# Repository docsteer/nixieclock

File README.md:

# Toms Nixie Clock
This project includes software and hardware designs for a nixie clock based on Raspberry Pi Zero W and IN14 tubes.

The design has hour, minute and second displays, separator digits (IN-1 indicators), and RGB LED underlighting of the tubes.

# Hardware
The hardware folder includes the PCB design files (KiCad format), and a bill of materials with component links to Mouser electronics.

# Software
The software is a Python script that runs on a standard installation of Raspian on a raspberry pi zero W.

It drives the tubes, and controls the LED underlighting based on astrononical time, pre-dawn, after dawn, after noon, after sunset)

It requires the following libraries (which you can install with ```pip install xxx```):

- spidev
- astral
- pytz
- neopixel

# Enclosure
The enclosure design is for laser-cut plywood with suitable openings for the tubes, indicators and support hardware

# License
This project is licensed under a Creative Commons Zero license. Feel free to remix and use as you please.

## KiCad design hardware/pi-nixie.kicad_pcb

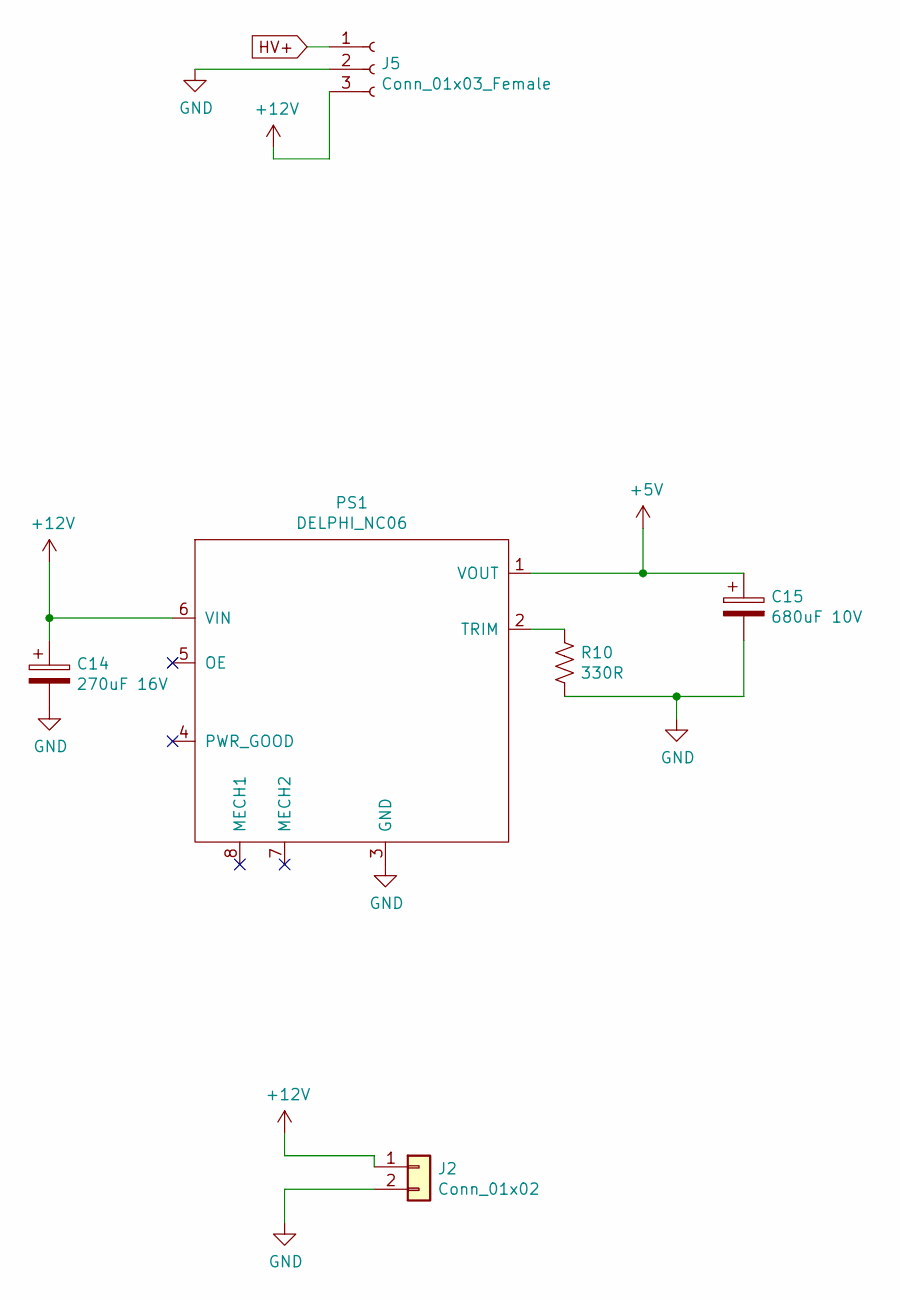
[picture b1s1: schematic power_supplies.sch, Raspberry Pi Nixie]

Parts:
C14: 270uF 16V; CP_Radial_D6.3mm_P2.50mm; Mouser P/N 232-16ZLJ270M6.3X11
C15: 680uF 10V; CP_Radial_D8.0mm_P3.50mm; Mouser P/N 710-860010274013
J2: Conn_01x02; SolderWirePad_1x02_P5.08mm_Drill1.5mm
J5: Conn_01x03_Female; PinHeader_1x03_P2.54mm_Vertical
PS1: DELPHI_NC06; DELPHI_NC06_REGULATOR
R10: 330R; R_1206_3216Metric_Pad1.42x1.75mm_HandSolder

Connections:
+5V: C15.1, PS1.1 (VOUT); also elsewhere on the board
+12V: C14.1, J2.1, J5.3, PS1.6 (VIN); also elsewhere on the board
GND: C14.2, C15.2, J2.2, J5.2, PS1.3 (GND), R10.2; also elsewhere on the board
HV+: J5.1; also elsewhere on the board
unnamed: PS1.2 (TRIM), R10.1

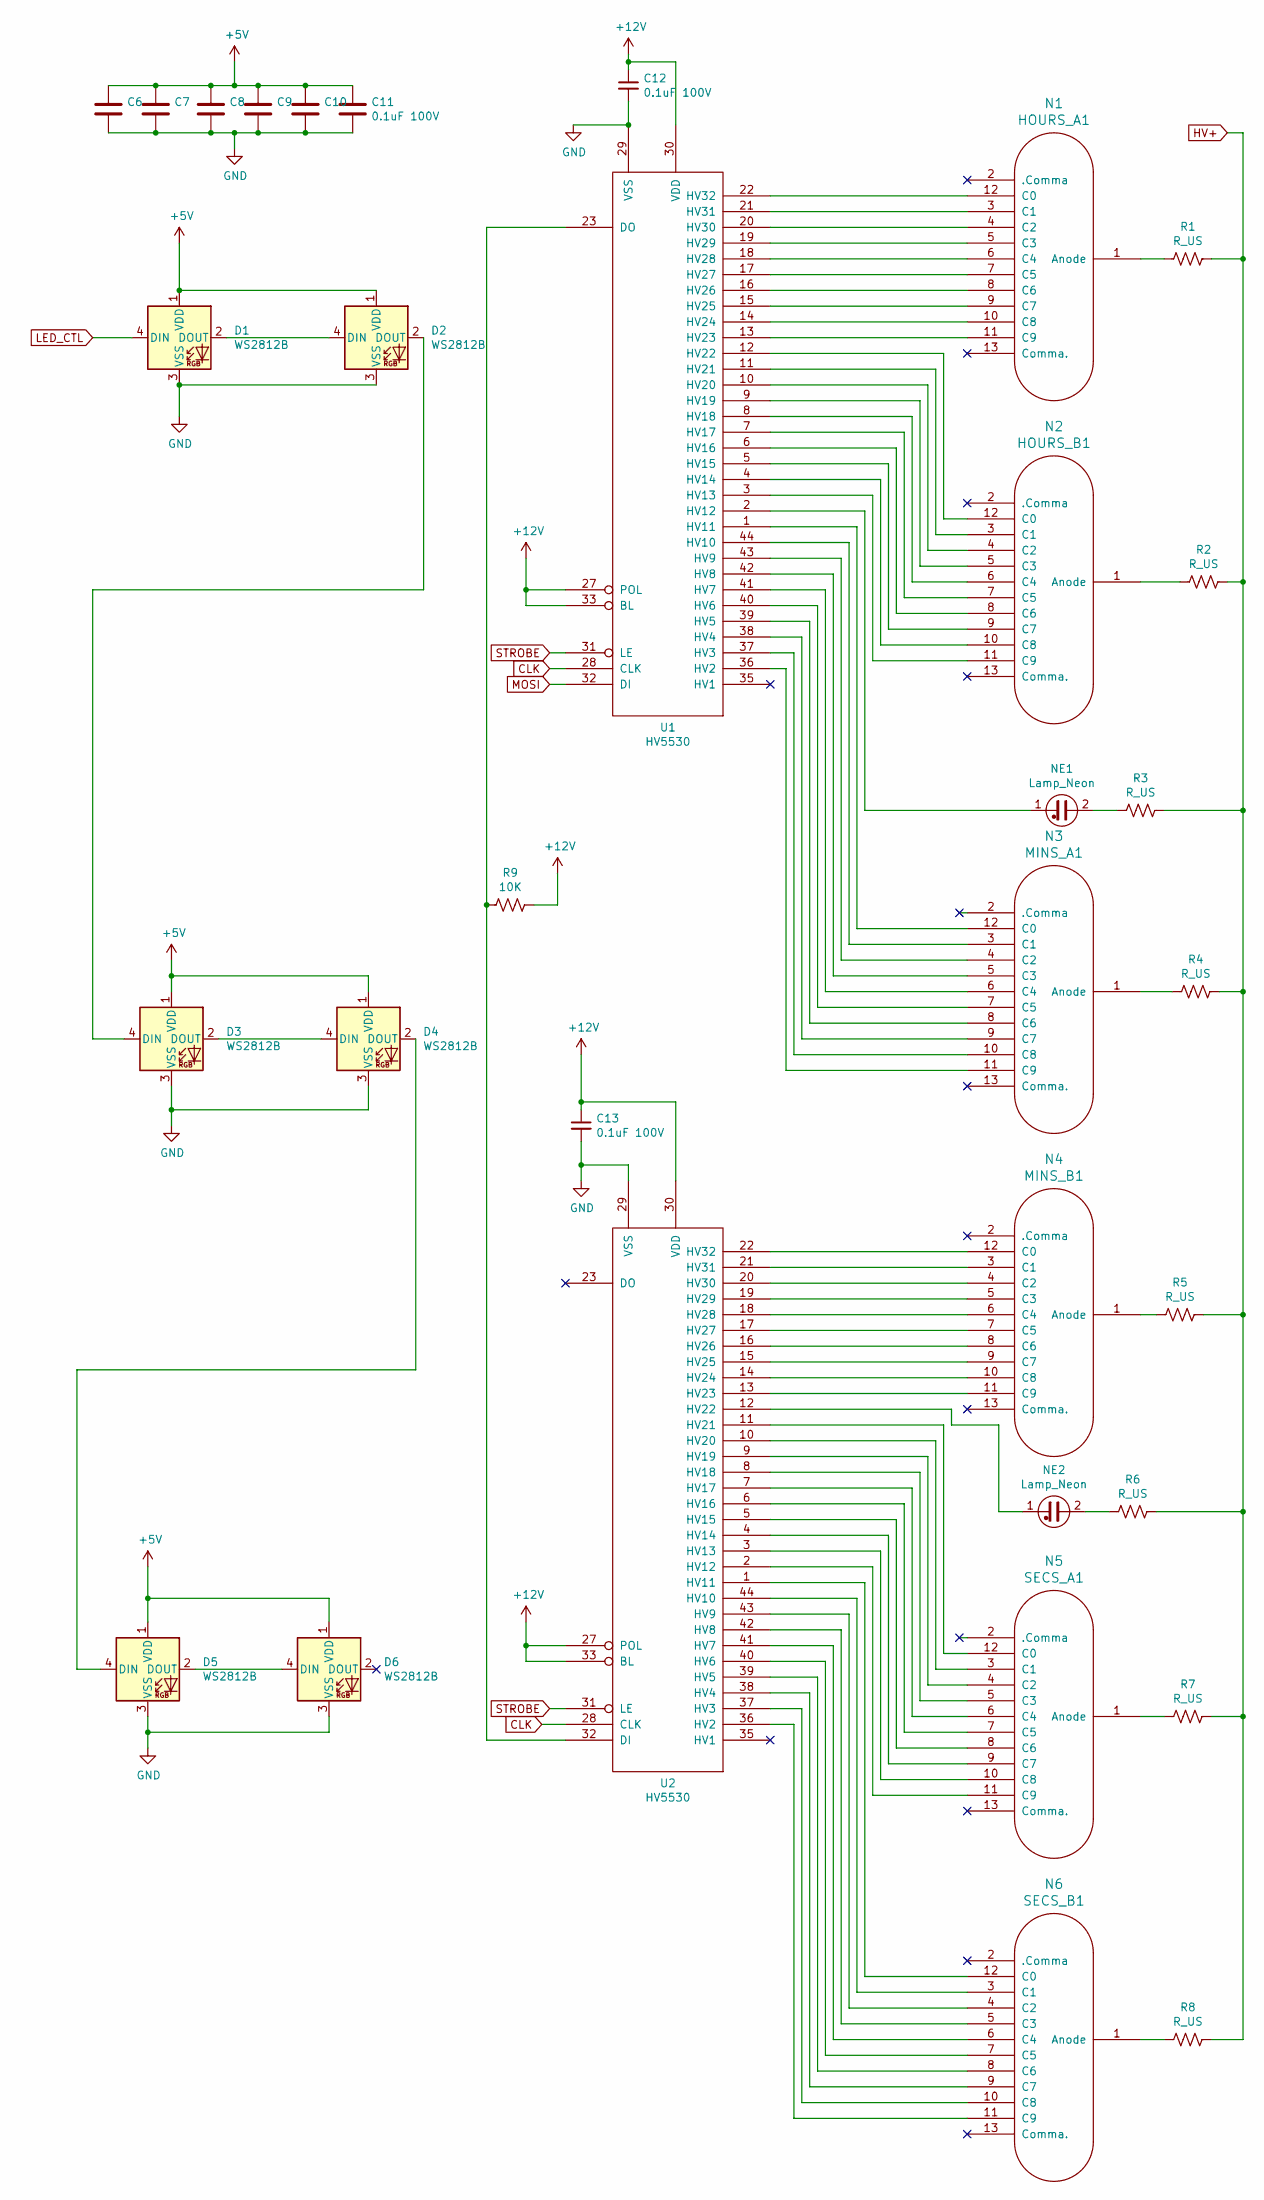
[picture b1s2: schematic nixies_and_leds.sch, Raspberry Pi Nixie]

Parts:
C6, C7, C8, C9, C10, C11, C12, C13: 0.1uF 100V; C_0805_2012Metric; Mouser P/N 710-885012207128
D1, D2, D3, D4, D5, D6: WS2812B; LED_WS2812B_PLCC4_5.0x5.0mm_P3.2mm; Mouser P/N 474-COM-13667
N1: HOURS_A1; IN-14-mod
N2: HOURS_B1; IN-14-mod
N3: MINS_A1; IN-14-mod
N4: MINS_B1; IN-14-mod
N5: SECS_A1; IN-14-mod
N6: SECS_B1; IN-14-mod
NE1, NE2: Lamp_Neon; IN-3
R1, R2, R3, R4, R5, R6, R7, R8: R_US; R_Axial_DIN0207_L6.3mm_D2.5mm_P10.16mm_Horizontal
R9: 10K; R_1206_3216Metric_Pad1.42x1.75mm_HandSolder
U1, U2: HV5530; PQFP-44_10x10mm_P0.8mm; Mouser P/N 689-HV5530PG-G

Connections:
+5V: C6.1, C7.1, C8.1, C9.1, C10.1, C11.1, D1.1 (VDD), D2.1 (VDD), D3.1 (VDD), D4.1 (VDD), D5.1 (VDD), D6.1 (VDD); also elsewhere on the board
+12V: C12.1, C13.1, R9.1, U1.27 (POL), U1.30 (VDD), U1.33 (BL), U2.27 (POL), U2.30 (VDD), U2.33 (BL); also elsewhere on the board
CLK: U1.28 (CLK), U2.28 (CLK); also elsewhere on the board
GND: C6.2, C7.2, C8.2, C9.2, C10.2, C11.2, C12.2, C13.2, D1.3 (VSS), D2.3 (VSS), D3.3 (VSS), D4.3 (VSS), D5.3 (VSS), D6.3 (VSS), U1.29 (VSS), U2.29 (VSS); also elsewhere on the board
HV+: R1.1, R2.1, R3.1, R4.1, R5.1, R6.1, R7.1, R8.1; also elsewhere on the board
LED_CTL: D1.4 (DIN); also elsewhere on the board
MOSI: U1.32 (DI); also elsewhere on the board
unnamed: D1.2 (DOUT), D2.4 (DIN)
unnamed: D2.2 (DOUT), D3.4 (DIN)
unnamed: D3.2 (DOUT), D4.4 (DIN)
unnamed: D4.2 (DOUT), D5.4 (DIN)
unnamed: D5.2 (DOUT), D6.4 (DIN)
unnamed: N1.1 (Anode), R1.2
unnamed: N1.3 (C1), U1.21 (HV31)
unnamed: N1.4 (C2), U1.20 (HV30)
unnamed: N1.5 (C3), U1.19 (HV29)
unnamed: N1.6 (C4), U1.18 (HV28)
unnamed: N1.7 (C5), U1.17 (HV27)
unnamed: N1.8 (C6), U1.16 (HV26)
unnamed: N1.9 (C7), U1.15 (HV25)
unnamed: N1.10 (C8), U1.14 (HV24)
unnamed: N1.11 (C9), U1.13 (HV23)
unnamed: N1.12 (C0), U1.22 (HV32)
unnamed: N2.1 (Anode), R2.2
unnamed: N2.3 (C1), U1.11 (HV21)
unnamed: N2.4 (C2), U1.10 (HV20)
unnamed: N2.5 (C3), U1.9 (HV19)
unnamed: N2.6 (C4), U1.8 (HV18)
unnamed: N2.7 (C5), U1.7 (HV17)
unnamed: N2.8 (C6), U1.6 (HV16)
unnamed: N2.9 (C7), U1.5 (HV15)
unnamed: N2.10 (C8), U1.4 (HV14)
unnamed: N2.11 (C9), U1.3 (HV13)
unnamed: N2.12 (C0), U1.12 (HV22)
unnamed: N3.1 (Anode), R4.2
unnamed: N3.3 (C1), U1.44 (HV10)
unnamed: N3.4 (C2), U1.43 (HV9)
unnamed: N3.5 (C3), U1.42 (HV8)
unnamed: N3.6 (C4), U1.41 (HV7)
unnamed: N3.7 (C5), U1.40 (HV6)
unnamed: N3.8 (C6), U1.39 (HV5)
unnamed: N3.9 (C7), U1.38 (HV4)
unnamed: N3.10 (C8), U1.37 (HV3)
unnamed: N3.11 (C9), U1.36 (HV2)
unnamed: N3.12 (C0), U1.1 (HV11)
unnamed: N4.1 (Anode), R5.2
unnamed: N4.3 (C1), U2.21 (HV31)
unnamed: N4.4 (C2), U2.20 (HV30)
unnamed: N4.5 (C3), U2.19 (HV29)
unnamed: N4.6 (C4), U2.18 (HV28)
unnamed: N4.7 (C5), U2.17 (HV27)
unnamed: N4.8 (C6), U2.16 (HV26)
unnamed: N4.9 (C7), U2.15 (HV25)
unnamed: N4.10 (C8), U2.14 (HV24)
unnamed: N4.11 (C9), U2.13 (HV23)
unnamed: N4.12 (C0), U2.22 (HV32)
unnamed: N5.1 (Anode), R7.2
unnamed: N5.3 (C1), U2.10 (HV20)
unnamed: N5.4 (C2), U2.9 (HV19)
unnamed: N5.5 (C3), U2.8 (HV18)
unnamed: N5.6 (C4), U2.7 (HV17)
unnamed: N5.7 (C5), U2.6 (HV16)
unnamed: N5.8 (C6), U2.5 (HV15)
unnamed: N5.9 (C7), U2.4 (HV14)
unnamed: N5.10 (C8), U2.3 (HV13)
unnamed: N5.11 (C9), U2.2 (HV12)
unnamed: N5.12 (C0), U2.11 (HV21)
unnamed: N6.1 (Anode), R8.2
unnamed: N6.3 (C1), U2.44 (HV10)
unnamed: N6.4 (C2), U2.43 (HV9)
unnamed: N6.5 (C3), U2.42 (HV8)
unnamed: N6.6 (C4), U2.41 (HV7)
unnamed: N6.7 (C5), U2.40 (HV6)
unnamed: N6.8 (C6), U2.39 (HV5)
unnamed: N6.9 (C7), U2.38 (HV4)
unnamed: N6.10 (C8), U2.37 (HV3)
unnamed: N6.11 (C9), U2.36 (HV2)
unnamed: N6.12 (C0), U2.1 (HV11)
unnamed: NE1.1, U1.2 (HV12)
unnamed: NE1.2, R3.2
unnamed: NE2.1, U2.12 (HV22)
unnamed: NE2.2, R6.2
unnamed: R9.2, U1.23 (DO), U2.32 (DI)
STROBE: U1.31 (LE), U2.31 (LE); also elsewhere on the board

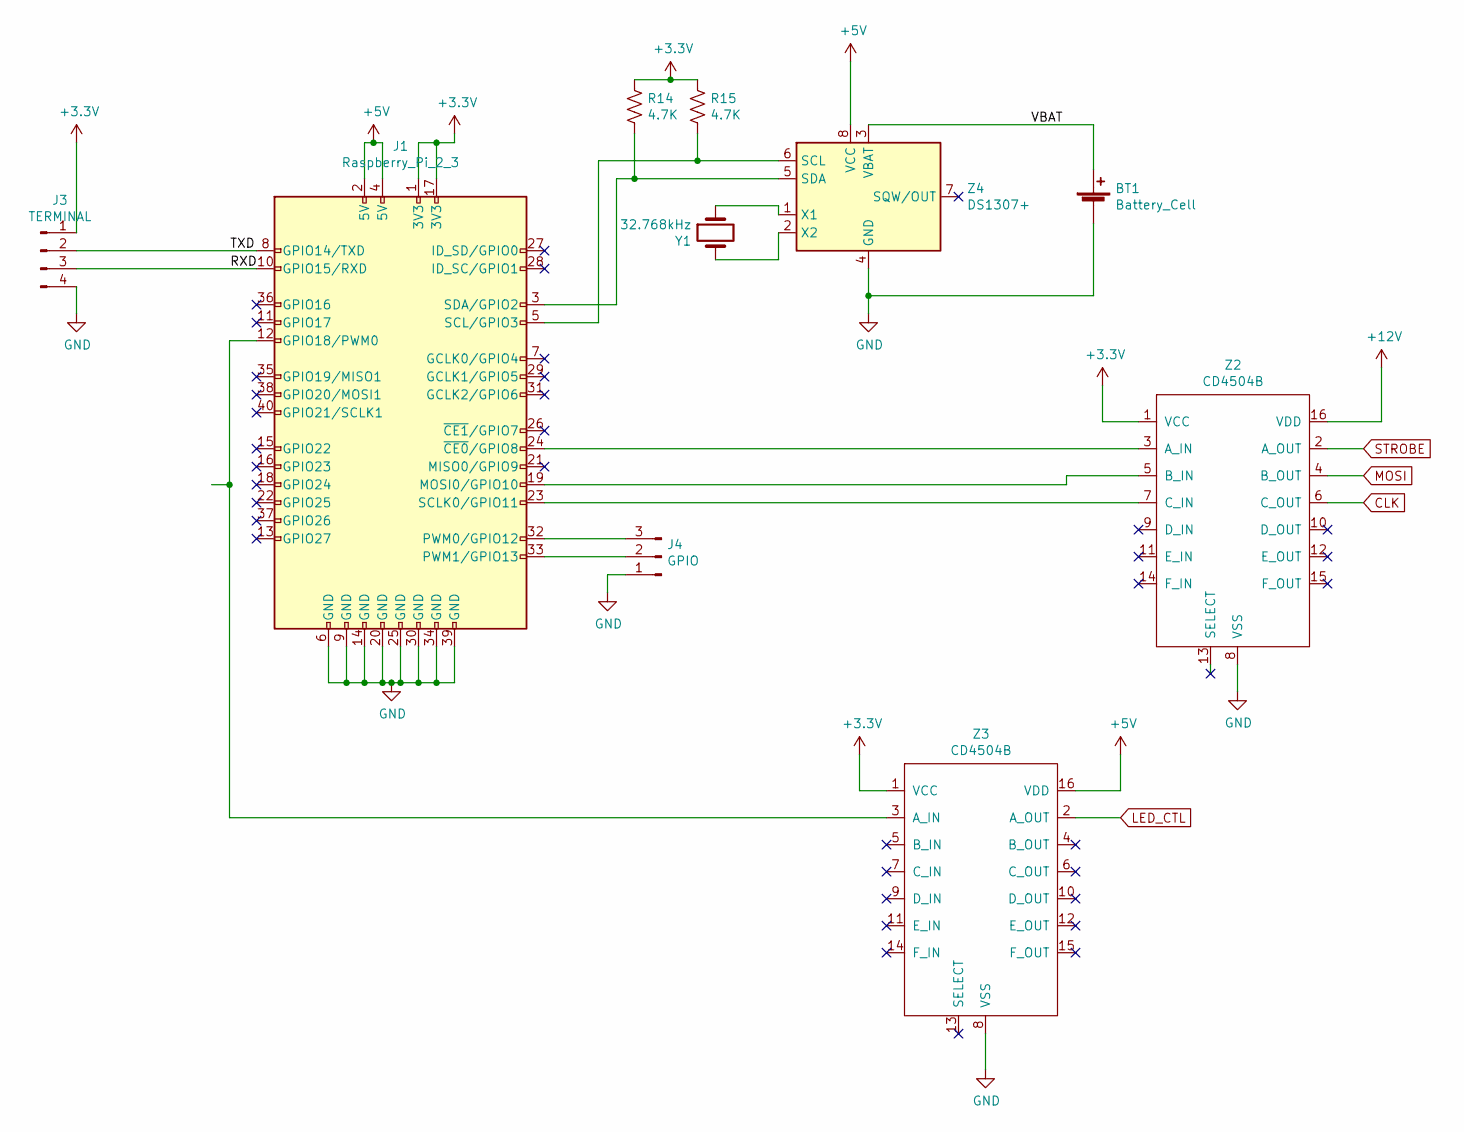
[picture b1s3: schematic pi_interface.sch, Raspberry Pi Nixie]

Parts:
BT1: Battery_Cell; BatteryHolder_Keystone_1058_1x2032
J1: Raspberry_Pi_2_3; Raspberry_Pi_Zero
J3: TERMINAL; PinHeader_1x04_P2.54mm_Horizontal
J4: GPIO; PinHeader_1x03_P2.54mm_Horizontal
R14, R15: 4.7K; R_1206_3216Metric_Pad1.42x1.75mm_HandSolder
Y1: 32.768kHz; Crystal_DS26_D2.0mm_L6.0mm_Horizontal; Mouser P/N 520-TFC2X6-X
Z2, Z3: CD4504B; SOIC-16_4.55x10.3mm_P1.27mm; Mouser P/N 595-CD4504BM96
Z4: DS1307+; SO-8_3.9x4.9mm_P1.27mm; Mouser P/N 700-DS1307Z

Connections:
+3V3: J1.1 (3V3), J1.17 (3V3), J3.1, R14.1, R15.1, Z2.1 (VCC), Z3.1 (VCC)
+5V: J1.2 (5V), J1.4 (5V), Z3.16 (VDD), Z4.8 (VCC); also elsewhere on the board
+12V: Z2.16 (VDD); also elsewhere on the board
/Pi Interface/RXD: J1.10 (GPIO15/RXD), J3.3
/Pi Interface/TXD: J1.8 (GPIO14/TXD), J3.2
/Pi Interface/VBAT: BT1.1 (+), Z4.3 (VBAT)
CLK: Z2.6 (C_OUT); also elsewhere on the board
GND: BT1.2 (-), J1.6 (GND), J1.9 (GND), J1.14 (GND), J1.20 (GND), J1.25 (GND), J1.30 (GND), J1.34 (GND), J1.39 (GND), J3.4, J4.1, Z2.8 (VSS), Z3.8 (VSS), Z4.4 (GND); also elsewhere on the board
LED_CTL: Z3.2 (A_OUT); also elsewhere on the board
MOSI: Z2.4 (B_OUT); also elsewhere on the board
unnamed: J1.3 (SDA/GPIO2), R14.2, Z4.5 (SDA)
unnamed: J1.5 (SCL/GPIO3), R15.2, Z4.6 (SCL)
unnamed: J1.12 (GPIO18/PWM0), Z3.3 (A_IN)
unnamed: J1.19 (MOSI0/GPIO10), Z2.5 (B_IN)
unnamed: J1.23 (SCLK0/GPIO11), Z2.7 (C_IN)
unnamed: J1.24 (~CE0~/GPIO8), Z2.3 (A_IN)
unnamed: J1.32 (PWM0/GPIO12), J4.3
unnamed: J1.33 (PWM1/GPIO13), J4.2
unnamed: Y1.1, Z4.1 (X1)
unnamed: Y1.2, Z4.2 (X2)
STROBE: Z2.2 (A_OUT); also elsewhere on the board

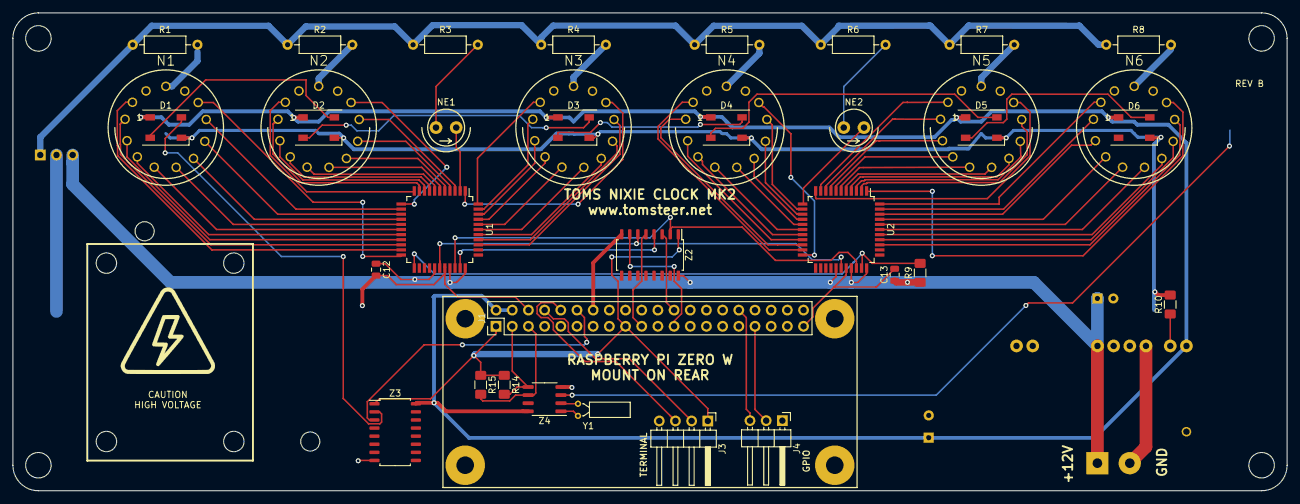
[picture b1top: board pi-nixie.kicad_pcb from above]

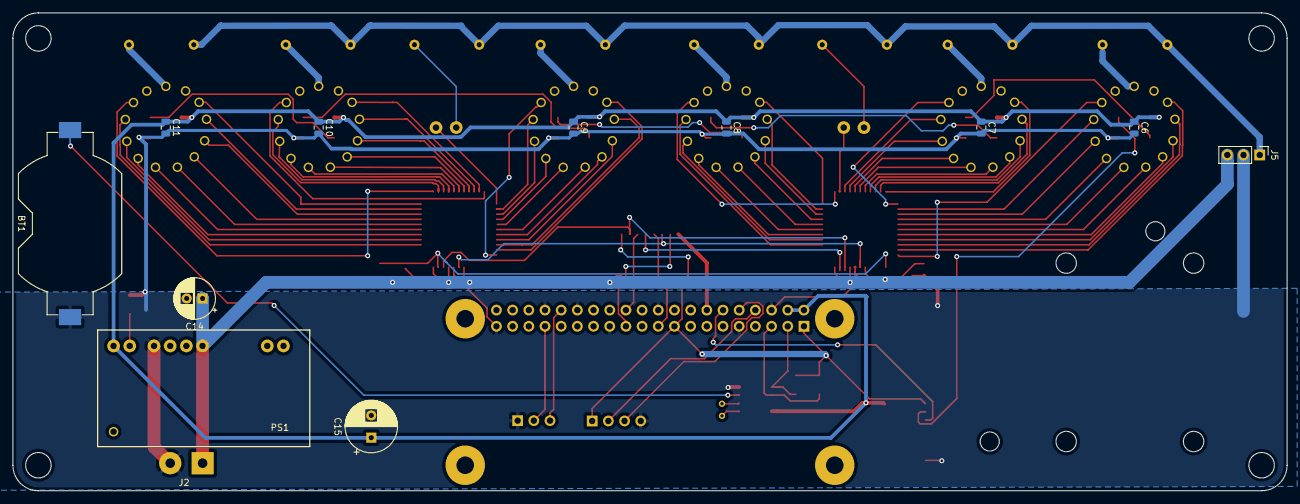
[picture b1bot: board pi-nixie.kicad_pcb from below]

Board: 2 copper layers, 199.9 x 74.9 mm, 49 parts (12 on the bottom side), 99 nets.
